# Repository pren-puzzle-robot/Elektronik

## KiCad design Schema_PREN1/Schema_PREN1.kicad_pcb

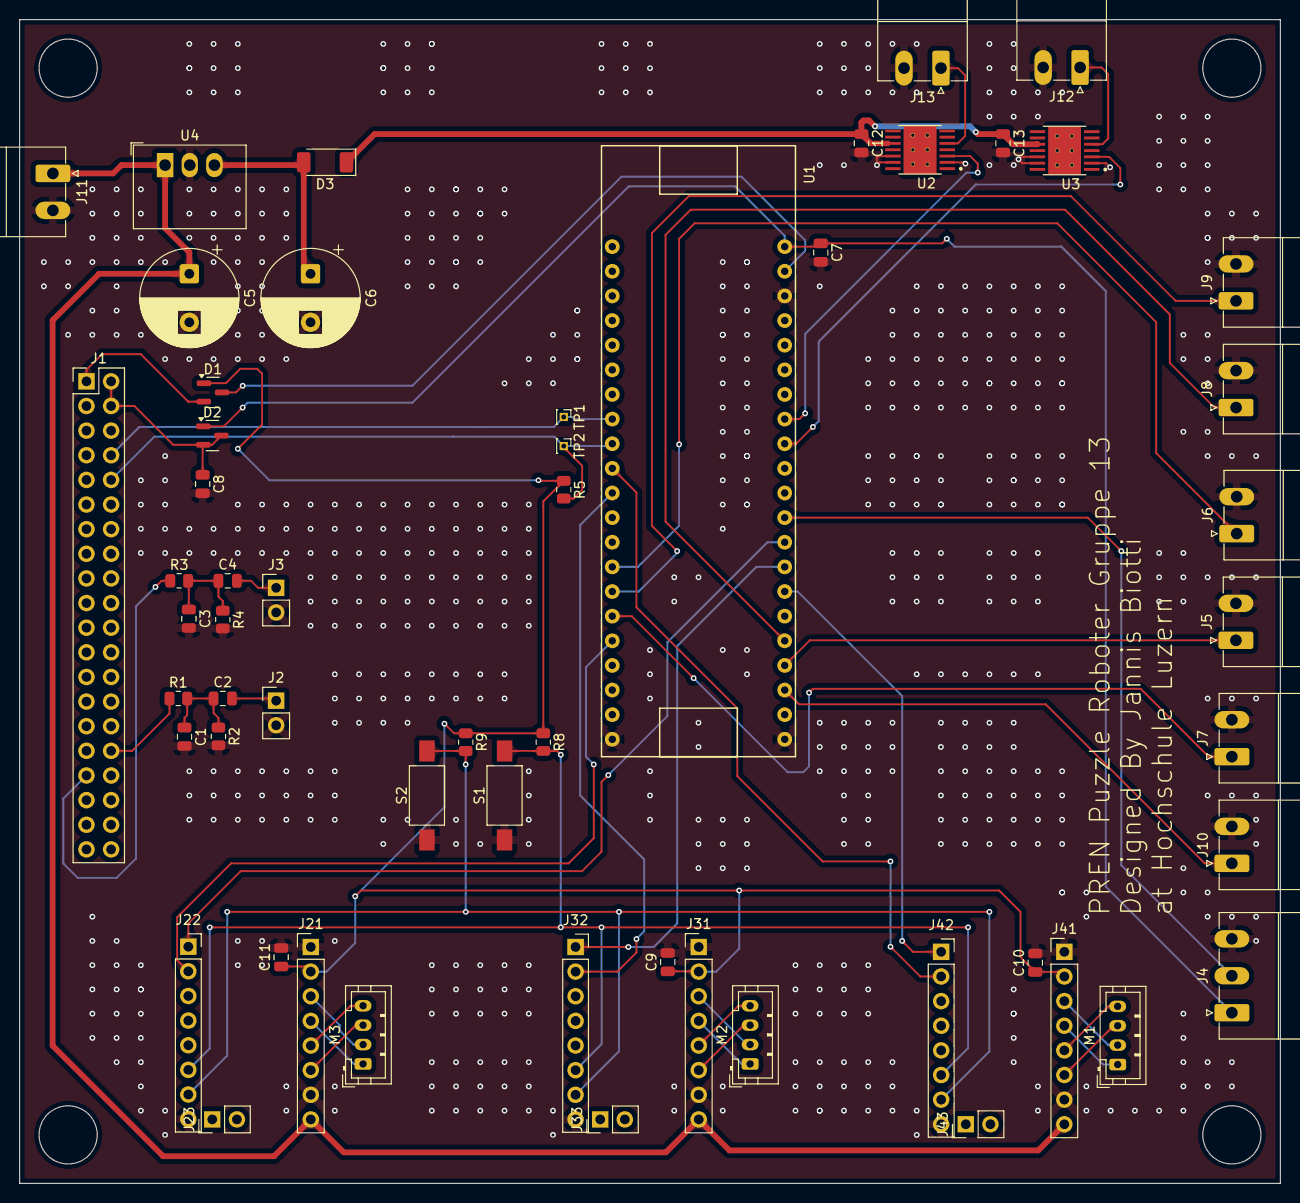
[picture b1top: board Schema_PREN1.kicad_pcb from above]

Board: 2 copper layers, 130.0 x 120.0 mm, 56 parts (0 on the bottom side), 48 nets.

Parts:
C1, C3: 470n; C_0805_2012Metric
C2, C4: 1u; C_0805_2012Metric
C5, C6: 10u; CP_Radial_D10.0mm_P5.00mm
C7, C8, C9, C10, C11, C12, C13: 100n; C_0805_2012Metric
D1, D2: BAT54C; SOT-23
D3: PMEG6020AELPX; D_SOD-128
J1: Rpi 4; PinHeader_2x20_P2.54mm_Vertical
J2: Lautsprecher 1; PinHeader_1x02_P2.54mm_Vertical
J3: Lautsprecher 2; PinHeader_1x02_P2.54mm_Vertical
J4: Pump/MotorDriver; PhoenixContact_MC_1,5_3-G-3.81_1x03_P3.81mm_Horizontal
J5, J6: Endswitch_X_Axis; PhoenixContact_MC_1,5_2-G-3.81_1x02_P3.81mm_Horizontal
J7, J10: Start/Stop_Btn; PhoenixContact_MC_1,5_2-G-3.81_1x02_P3.81mm_Horizontal
J8, J9: Endswitch_Y_Axis; PhoenixContact_MC_1,5_2-G-3.81_1x02_P3.81mm_Horizontal
J11: 24V_IN; PhoenixContact_MC_1,5_2-G-3.81_1x02_P3.81mm_Horizontal
J12, J13: Solenoid; PhoenixContact_MC_1,5_2-G-3.81_1x02_P3.81mm_Horizontal
J21, J31, J41: Left; PinHeader_1x08_P2.54mm_Vertical
J22, J32, J42: Right; PinSocket_1x08_P2.54mm_Vertical
J23, J33, J43: Bottom; PinHeader_1x02_P2.54mm_Vertical
M1: StepperX; JST_PH_B4B-PH-K_1x04_P2.00mm_Vertical
M2: StepperY; JST_PH_B4B-PH-K_1x04_P2.00mm_Vertical
M3: StepperRot; JST_PH_B4B-PH-K_1x04_P2.00mm_Vertical
R1, R3: 56; R_0805_2012Metric
R2, R4: 150; R_0805_2012Metric
R5, R8, R9: 10k; R_0805_2012Metric
S1: MS2_SEL; SW_SPST_FSMSM
S2: MS1_Sel; SW_SPST_FSMSM
TP1: UART RX; PinHeader_1x01_P1.00mm_Vertical
TP2: UART Tx; PinHeader_1x01_P1.00mm_Vertical
U1: tinyK22
U2, U3: TPS27S100A; IC_TPS27S100BPWPR
U4: R-78B12-1.0; Converter_DCDC_RECOM_R-78B-2.0_THT

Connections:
+3V3: C9.1, C10.1, C11.1, D1.1 (K), J21.2, J31.2, J41.2, R5.1, R8.1, R9.1
+3V3_rpi: D1.2 (A), J1.1
+5V: C7.1, D2.1 (K), J4.1, U1.42 (+5V)
+12V: C12.1, C13.1, D3.1 (K), U2.10, U3.10
+24V: C5.1, J11.1, J21.8, J31.8, J41.8, U4.1 (IN)
/Dir_Rot: J22.1, U1.30 (PTD2)
/Dir_X_Axis: J42.1, U1.28 (PTD0)
/Dir_Y_Axis: J32.1, U1.29 (PTD1)
/Endswitch_X_Axis_1: J5.1, U1.25 (PTC9)
/Endswitch_X_Axis_2: J6.1, U1.14 (PTB0)
/Endswitch_Y_Axis_1: J8.1, U1.26 (PTC10)
/Endswitch_Y_Axis_2: J9.1, U1.15 (PTB1)
/MS1: J22.7, J32.7, J42.7, R9.2, S2.2
/MS2: J22.6, J32.6, J42.6, R8.2, S1.2
/PWM_0: J1.32, R1.1
/PWM_1: J1.33, R3.1
/Preassure_Release_Valve: U1.34 (PTD6), U3.3
/Pump_Suck: J4.2, U1.31 (PTD3)
/Solenoid: U1.35 (PTD7), U2.3
/Solenoid_12V: J13.1, U2.5
/Start_Btn: J10.1, U1.24 (PTC8)
/Step_Rot: J22.2, U1.17 (PTB3)
/Step_X_Axis: J42.2, U1.10 (PTA4)
/Step_Y_Axis: J32.2, U1.11 (PTA5)
/Stop_Btn: J7.1, U1.16 (PTB2)
/TMC2209_SilentStepStickRot/M1A: J21.4, M3.1
/TMC2209_SilentStepStickRot/M1B: J21.3, M3.2
/TMC2209_SilentStepStickRot/M2A: J21.6, M3.3
/TMC2209_SilentStepStickRot/M2B: J21.5, M3.4
/TMC2209_SilentStepStickX/M1A: J41.4, M1.1
/TMC2209_SilentStepStickX/M1B: J41.3, M1.2
/TMC2209_SilentStepStickX/M2A: J41.6, M1.3
/TMC2209_SilentStepStickX/M2B: J41.5, M1.4
/TMC2209_SilentStepStickY/M1A: J31.4, M2.1
/TMC2209_SilentStepStickY/M1B: J31.3, M2.2
/TMC2209_SilentStepStickY/M2A: J31.6, M2.3
/TMC2209_SilentStepStickY/M2B: J31.5, M2.4
/TinyRx: J1.8, TP1.1, U1.8 (PTA1)
/TinyTx: J1.10, R5.2, TP2.1, U1.9 (PTA2)
/Tiny_3V3: D1.3 (A), U1.41 (+3V3)
/Valve_12V: J12.1, U3.5
GND: C1.2, C3.2, C5.2, C6.2, C7.2, C8.2, C9.2, C10.2, C11.2, C12.2, C13.2, J2.2, J3.2, J4.3, J5.2, J6.2, J7.2, J8.2, J9.2, J10.2, J11.2, J12.2, J13.2, J21.1, J21.7, J22.8, J31.1, J31.7, J32.8, J41.1, J41.7, J42.8, R2.2, R4.2, S1.1, S2.1, U1.21 (GND), U1.22 (GND), U1.40 (GND), U2.2, U2.12, U2.13, U3.2, U3.12, U3.13, U4.2 (GND)
unnamed: C1.1, C2.1, R1.2, R2.1
unnamed: C3.1, C4.1, R3.2, R4.1
unnamed: C6.1, D3.2 (A), U4.3 (OUT)
unnamed: C8.1, D2.2 (A), D2.3 (A), J1.2, J1.4
unnamed: C2.2, J2.1
unnamed: C4.2, J3.1

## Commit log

2025-11-07 added MK22 symbol
2025-11-07 Add .gitignore file
2025-11-11 Add Library with TinyK22 footprint and symbol
2025-11-29 Expand Schematic
2025-11-30 Finish V1 of Schematic
2026-02-20 Schema: änderungen
2026-02-22 Add SW_TinyK22 MCUXpresso project and update gitignore
2026-03-08 Schematic: Update Schematic
2026-03-08 Schematic: Updating Names and Footprint selection
2026-03-08 Schematic,PCB: Update Footprints and Start Work on PCB
2026-03-11 Schematic: Start making connections
2026-03-12 added state machine, OIs (Pump and Solenoid) with functions, UART0
2026-03-15 PCB: Finished up PCB Ready to order
2026-03-19 added camond handling via Uart
2026-04-15 Updated motor control, implemented Endschalter and cleaned up unused files
2026-04-24 Update IO config: pull-up + falling edge
2026-04-25 added reset function and more
2026-04-28 debug and stuff
2026-05-20 improvements
